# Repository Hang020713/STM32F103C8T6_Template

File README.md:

# About This Project

A custom STM32F103C8T6 PCB template designed for hand-soldering, prototyping, and embedded system development.
This board serves as a solid starting point for STM32-based projects, robotics systems, and embedded applications.

---

# 📟 Board Preview

![[pcb]](/images/pcb.png)

---

# 📁 File Structure

<!-- TREEVIEW START -->
```bash
├── stm32f103c8t6.kicad_pcb   # PCB Layout
├── stm32f103c8t6.kicad_pro   # KiCad Project File
├── stm32f103c8t6.kicad_sch   # Schematic
└── README.md
```

## File Descriptions
* `kicad_pcb` - PCB Layout
* `kicad_sch` - Schematic
* `kicad_pro` - KiCad Project Configuration File
<!-- TREEVIEW END -->

---

# 🚀 Getting Started

Requirements
* KiCad 8 (recommended)

Open the `.kicad_pro` file using KiCad 8 to access the full project including schematic and PCB layout.

---

# 🔧 Board Feature

STM32 Board have below features
- [x] Hand-solder friendly footprint design
- [x] 5V Voltage Regulator
- [x] Micro USB Connector
- [x] 1 x UART Interface
- [x] 1 x I2C Interface
- [x] BOOT Button
- [x] SWD Debugging Interface
- [x] 16 MHz External Crystal Oscillator
- [ ] USB-C Connector

---

# 🧠 Usage

STM32 have a deep potential. You could modify this board to extend more pins you want. Example:

* Expose additional GPIO Pins
* Add SPI peripherals
* Integreate sensors (IMU, barometer, etc.)
* Add motor drivers

---

# License

MIT License

Feel free to use, modify, and distribute.

---

## 📫 Let's Connect

I'm always interested in collaborating on embedded systems projects, robotics competitions, or autonomous vehicle development!

---

<p align="right">(<a href="#readme-top">Back to Top</a>)</p>

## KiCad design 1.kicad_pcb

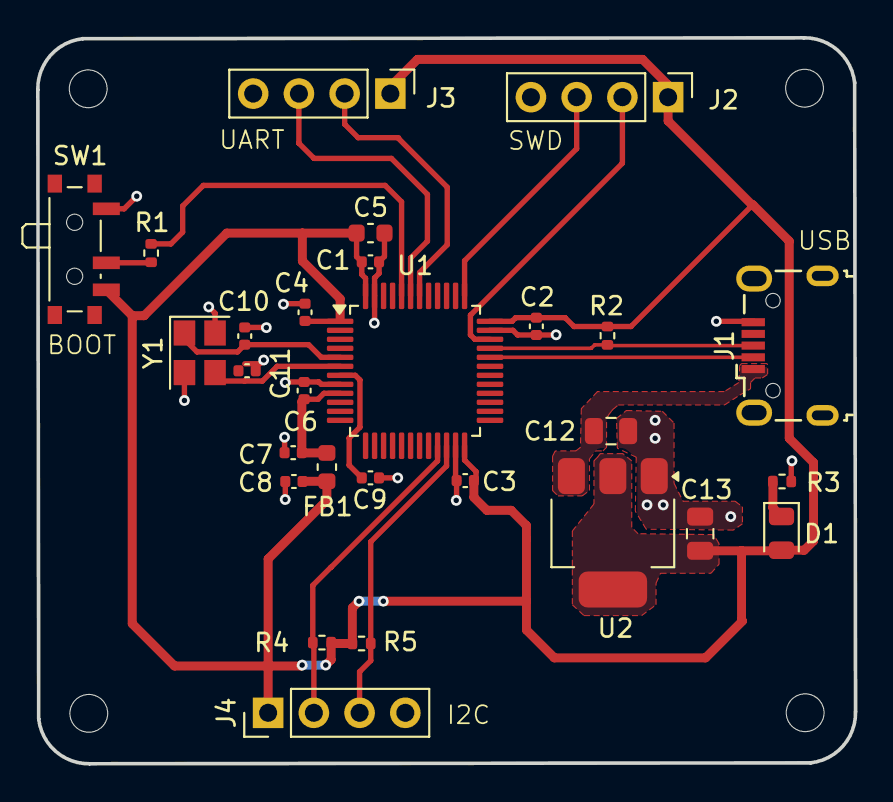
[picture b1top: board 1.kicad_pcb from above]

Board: 2 copper layers, 45.4 x 40.3 mm, 32 parts (0 on the bottom side), 18 nets.

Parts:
C1, C2, C3, C4, C9: 100n; C_0402_1005Metric
C5: 10u; C_0603_1608Metric
C6: 10n; C_0402_1005Metric
C7, C8: 1u; C_0402_1005Metric
C10, C11: 10p; C_0402_1005Metric
C12, C13: 22u; C_0805_2012Metric
D1: LED; LED_0805_2012Metric
FB1: 120R; L_0603_1608Metric
H1, H2, H3, H4: MountingHole; MountingHole_2.1mm
J1: USB_B_Micro; USB_Micro-B_Wuerth_629105150521
J2, J3, J4: Conn_01x04_Pin; PinHeader_1x04_P2.54mm_Vertical
R1: 10k; R_0402_1005Metric
R2, R3, R4, R5: 1k5; R_0402_1005Metric
SW1: SW_SPDT; SW_SPDT_PCM12
U1: STM32F103C8T6; LQFP-48_7x7mm_P0.5mm
U2: AMS1117-3.3; SOT-223-3_TabPin2
Y1: 16MHz; Crystal_SMD_3225-4Pin_3.2x2.5mm

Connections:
+3.3V: C1.1, C2.1, C3.1, C4.1, C5.1, C8.1, C13.1, D1.2 (A), FB1.1, J2.1, J3.1, J4.1, R2.1, R4.1, R5.1, SW1.3 (C), U1.1 (VBAT), U1.24 (VDD), U1.36 (VDD), U1.48 (VDD), U2.2 (VO)
+3.3VA: C6.1, C7.1, FB1.2, U1.9 (VDDA)
/BOOT0: R1.2, U1.44 (BOOT0)
/HSE_IN: C10.1, U1.5 (PD0), Y1.1
/HSE_OUT: C11.1, U1.6 (PD1), Y1.3
/I2C2_SCL: J4.3, R5.2, U1.22 (PB11)
/I2C2_SDA: J4.2, R4.2, U1.21 (PB10)
/NRST: C9.1, U1.7 (NRST)
/PWR_LED_K: D1.1 (K), R3.1
/SWCLK: J2.3, U1.37 (PA14)
/SWDIO: J2.2, U1.34 (PA13)
/USART1_RX: J3.3, U1.43 (PB7)
/USART1_TX: J3.2, U1.42 (PB6)
/USE_D+: J1.3 (D+), R2.2, U1.33 (PA12)
/USE_D-: J1.2 (D-), U1.32 (PA11)
GND: C1.2, C2.2, C3.2, C4.2, C5.2, C6.2, C7.2, C8.2, C9.2, C10.2, C11.2, C12.2, C13.2, J1.5 (GND), J2.4, J3.4, J4.4, R3.2, SW1.1 (A), U1.8 (VSSA), U1.23 (VSS), U1.35 (VSS), U1.47 (VSS), U2.1 (GND), Y1.2, Y1.4
unnamed: R1.1, SW1.2 (B)
VBUS: C12.1, J1.1 (VBUS), U2.3 (VI)

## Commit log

2025-03-23 Update V1
2025-06-15 Add 2x2 keyboards
2026-04-12 chore: tidy repo format
    - Update git ignore
    - Remove backup files
    - Tidy Readme
2026-04-12 fix: remove banner photo in readme
2026-04-12 feat: add MIT License
2026-04-17 feat: update readme images
    Added board preview section
2026-04-17 chore: kicad_pro
